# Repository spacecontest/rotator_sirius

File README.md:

# Направленная антенна с поворотным устройством для приема сигналов спутников
[Сайт проекта](http://openkoda.tilda.ws)

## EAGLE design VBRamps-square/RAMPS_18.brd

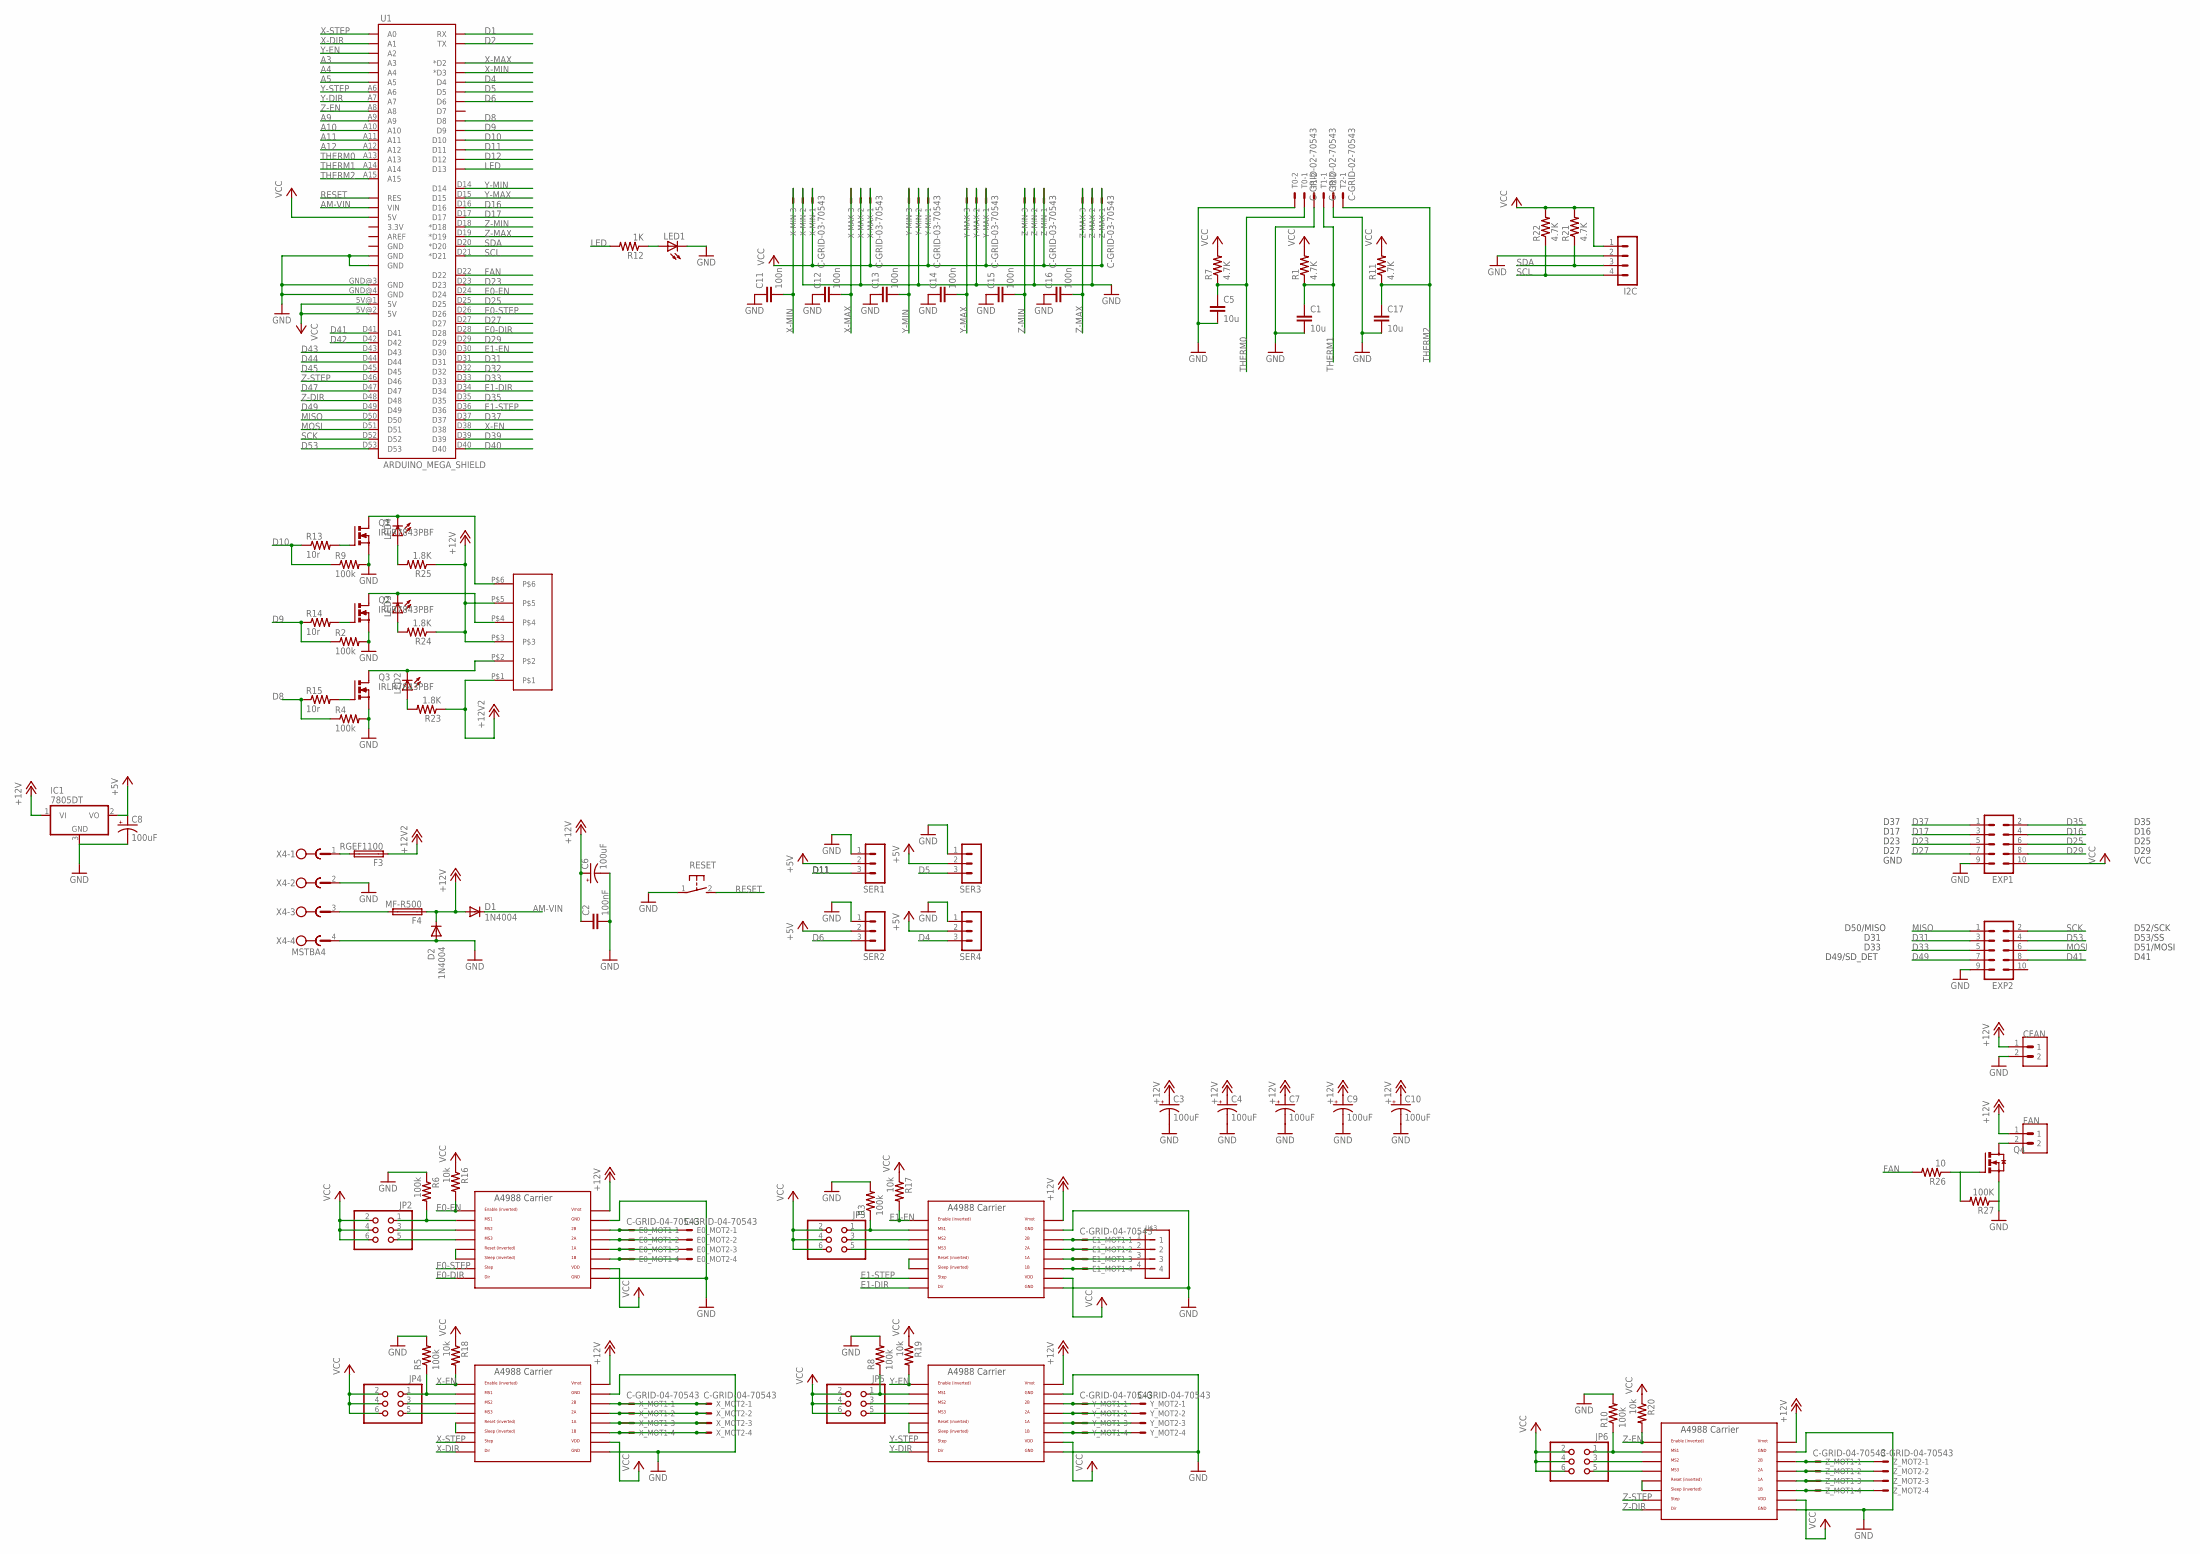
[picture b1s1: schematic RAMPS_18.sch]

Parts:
C1, C5, C17: 10u; C1206
C2: 100nF; C0805
C3, C4, C6, C7, C8, C9, C10: 100uF; 153CLV-0605
C11, C12, C13, C14, C15, C16: 100n; C0805
CFAN: CWF-2_D; CWF-2_P
D1, D2: 1N4004; DO41-10
E0_MOT1, E0_MOT2, E1_MOT1: C-GRID-04-70543; 70543-04
EXP1, EXP2: MA05-2; PAK100/2500-10
F3: RGEF1100
F4: MF-R500
FAN: CWF-2_D; CWF-2_P
HEAT_PORT: 282837-6
I2C: MA04-1
IC1: 7805DT; TO252
JP2, JP3, JP4, JP5, JP6: PINHD-2X3; 2X03
LED1, LED2, LED3, LED4: LEDCHIP-LED0805; CHIP-LED0805
Q1, Q2, Q3: IRLR7843PBF; D-PAK_TO252AA
Q4: N_MOSFET_SOT23; SOT23
R1, R7, R11, R21, R22: 4.7K; R1206
R2, R4, R9: 100k; R0805
R3, R5, R6, R8, R10: 100k; R1206
R12: 1K; R0805
R13, R15: 10r; R0805
R14: 10r; M0805
R16, R17, R18, R19, R20: 10k; R1206
R23, R24, R25: 1.8K; R0805
R26: 10; R1206
R27: 100K; R1206
RESET: 31-XX; B3F-31XX
SER1, SER2, SER3, SER4: 3PIN-HEADER
T0, T1, T2: C-GRID-02-70543; 70543-02
U1: ARDUINO_MEGA_SHIELD
U$3: CWF-4_D; CWF-4_P
U$4, U$5, U$6, U$7, U$8: A4988BREAKOUT
X4: MSTBA4
X-MAX: C-GRID-03-70543; 70543-03
X-MIN: C-GRID-03-70543; 70543-03
X_MOT1, X_MOT2: C-GRID-04-70543; 70543-04
Y-MAX: C-GRID-03-70543; 70543-03
Y-MIN: C-GRID-03-70543; 70543-03
Y_MOT1, Y_MOT2: C-GRID-04-70543; 70543-04
Z-MAX: C-GRID-03-70543; 70543-03
Z-MIN: C-GRID-03-70543; 70543-03
Z_MOT1, Z_MOT2: C-GRID-04-70543; 70543-04

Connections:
+5V: C8.+, IC1.2 (VO), SER1.2, SER2.2, SER3.2, SER4.2
+12V: C2.1, C3.+, C4.+, C6.+, C7.+, C9.+, C10.+, CFAN.1, D1.A, D2.C, F4.P$1 (1), FAN.1, HEAT_PORT.P$3, HEAT_PORT.P$5, IC1.1 (VI), R24.1, R25.1, U$4.VMOT, U$5.VMOT, U$6.VMOT, U$7.VMOT, U$8.VMOT
+12V2: F3.P$1 (1), HEAT_PORT.P$1, R23.1
A3: U1.A3
A4: U1.A4
A5: U1.A5
A9: U1.A9
A10: U1.A10
A11: U1.A11
A12: U1.A12
AM-VIN: D1.C, U1.VIN
D1: U1.RX
D2: U1.TX
D4: SER4.3, U1.D4
D5: SER3.3, U1.D5
D6: SER2.3, U1.D6
D8: R4.1, R15.1, U1.D8
D9: R2.1, R14.1, U1.D9
D10: R9.1, R13.1, U1.D10
D11: SER1.3, U1.D11
D12: U1.D12
D16: EXP1.4, U1.D16
D17: EXP1.3, U1.D17
D23: EXP1.5, U1.D23
D25: EXP1.6, U1.D25
D27: EXP1.7, U1.D27
D29: EXP1.8, U1.D29
D31: EXP2.3, U1.D31
D32: U1.D32
D33: EXP2.5, U1.D33
D35: EXP1.2, U1.D35
D37: EXP1.1, U1.D37
D39: U1.D39
D40: U1.D40
D41: EXP2.8, U1.D41
D42: U1.D42
D43: U1.D43
D44: U1.D44
D45: U1.D45
D47: U1.D47
D49: EXP2.7, U1.D49
D53: EXP2.4, U1.D53
E0-DIR: U1.D28, U$4.DIR
E0-EN: R16.2, U1.D24, U$4.EN
E0-STEP: U1.D26, U$4.STEP
E1-DIR: U1.D34, U$5.DIR
E1-EN: R17.2, U1.D30, U$5.EN
E1-STEP: U1.D36, U$5.STEP
FAN: R26.2, U1.D22
GND: C1.2, C2.2, C3.-, C4.-, C5.2, C6.-, C7.-, C8.-, C9.-, C10.-, C11.1, C12.1, C13.1, C14.1, C15.1, C16.1, C17.2, CFAN.2, D2.A, EXP1.9, EXP2.9, I2C.2, IC1.3 (GND), LED1.C, Q1.3 (S), Q2.3 (S), Q3.3 (S), Q4.2 (S), R2.2, R3.2, R4.2, R5.2, R6.1, R8.2, R9.2, R10.2, R27.1, RESET.1, SER1.1, SER2.1, SER3.1, SER4.1, T0.2, T1.2, T2.2, U1.GND@0 (GND), U1.GND@1 (GND), U1.GND@3 (GND), U1.GND@4 (GND), U$4.GND, U$4.GND@0 (GND), U$5.GND, U$5.GND@0 (GND), U$6.GND, U$6.GND@0 (GND), U$7.GND, U$7.GND@0 (GND), U$8.GND, U$8.GND@0 (GND), X4.2, X4.4, X-MAX.2, X-MIN.2, Y-MAX.2, Y-MIN.2, Z-MAX.2, Z-MIN.2
LED: R12.2, U1.D13
MISO: EXP2.1, U1.D50
MOSI: EXP2.6, U1.D51
unnamed: HEAT_PORT.P$4, LED3.C, Q2.4 (D)
unnamed: E0_MOT1.1, E0_MOT2.1, U$4.2B
unnamed: E0_MOT1.2, E0_MOT2.2, U$4.2A
unnamed: JP2.1, R6.2, U$4.MS1
unnamed: JP2.5, U$4.MS3
unnamed: HEAT_PORT.P$6, LED4.C, Q1.4 (D)
unnamed: U$4.RST, U$4.SLP (SLEEP)
unnamed: JP2.3, U$4.MS2
unnamed: E0_MOT1.3, E0_MOT2.3, U$4.1A
unnamed: E0_MOT1.4, E0_MOT2.4, U$4.1B
unnamed: E1_MOT1.1, U$3.1, U$5.2B
unnamed: E1_MOT1.2, U$3.2, U$5.2A
unnamed: JP4.1, R5.1, U$6.MS1
unnamed: JP4.3, U$6.MS2
unnamed: E1_MOT1.3, U$3.3, U$5.1A
unnamed: JP5.3, U$7.MS2
unnamed: E1_MOT1.4, U$3.4, U$5.1B
unnamed: JP4.5, U$6.MS3
unnamed: U$6.RST, U$6.SLP (SLEEP)
unnamed: U$6.2B, X_MOT1.1, X_MOT2.1
unnamed: U$6.2A, X_MOT1.2, X_MOT2.2
unnamed: U$7.RST, U$7.SLP (SLEEP)
unnamed: U$5.RST, U$5.SLP (SLEEP)
unnamed: JP3.1, R3.1, U$5.MS1
unnamed: U$6.1A, X_MOT1.3, X_MOT2.3
unnamed: U$6.1B, X_MOT1.4, X_MOT2.4
unnamed: U$7.2B, Y_MOT1.1, Y_MOT2.1
unnamed: U$7.2A, Y_MOT1.2, Y_MOT2.2
unnamed: U$7.1A, Y_MOT1.3, Y_MOT2.3
unnamed: JP5.5, U$7.MS3
unnamed: LED2.A, R23.2
unnamed: JP5.1, R8.1, U$7.MS1
unnamed: JP3.5, U$5.MS3
unnamed: JP3.3, U$5.MS2
unnamed: U$7.1B, Y_MOT1.4, Y_MOT2.4
unnamed: JP6.3, U$8.MS2
unnamed: U$8.RST, U$8.SLP (SLEEP)
unnamed: JP6.5, U$8.MS3
unnamed: JP6.1, R10.1, U$8.MS1
unnamed: U$8.2B, Z_MOT1.1, Z_MOT2.1
unnamed: U$8.2A, Z_MOT1.2, Z_MOT2.2
unnamed: U$8.1A, Z_MOT1.3, Z_MOT2.3
unnamed: U$8.1B, Z_MOT1.4, Z_MOT2.4
unnamed: LED3.A, R24.2
unnamed: LED1.A, R12.1
unnamed: Q2.1 (G), R14.2
unnamed: Q1.1 (G), R13.2
unnamed: Q3.1 (G), R15.2
unnamed: LED4.A, R25.2
unnamed: HEAT_PORT.P$2, LED2.C, Q3.4 (D)
unnamed: F3.P$2 (2), X4.1
unnamed: F4.P$2 (2), X4.3
unnamed: FAN.2, Q4.3 (D)
unnamed: Q4.1 (G), R26.1, R27.2
RESET: RESET.2 (S), U1.RES
SCK: EXP2.2, U1.D52
SCL: I2C.4, R22.1, U1.D21 (*D21)
SDA: I2C.3, R21.1, U1.D20 (*D20)
THERM0: C5.1, R7.1, T0.1, U1.A13
THERM1: C1.1, R1.1, T1.1, U1.A14
THERM2: C17.1, R11.1, T2.1, U1.A15
VCC: EXP1.10, I2C.1, JP2.2, JP2.4, JP2.6, JP3.2, JP3.4, JP3.6, JP4.2, JP4.4, JP4.6, JP5.2, JP5.4, JP5.6, JP6.2, JP6.4, JP6.6, R1.2, R7.2, R11.2, R16.1, R17.1, R18.1, R19.1, R20.1, R21.2, R22.2, U1.5V@0 (5V), U1.5V@1 (5V), U1.5V@2 (5V), U$4.VDD, U$5.VDD, U$6.VDD, U$7.VDD, U$8.VDD, X-MAX.1, X-MIN.1, Y-MAX.1, Y-MIN.1, Z-MAX.1, Z-MIN.1
X-DIR: U1.A1, U$6.DIR
X-EN: R18.2, U1.D38, U$6.EN
X-MAX: C12.2, U1.D2 (*D2), X-MAX.3
X-MIN: C11.2, U1.D3 (*D3), X-MIN.3
X-STEP: U1.A0, U$6.STEP
Y-DIR: U1.A7, U$7.DIR
Y-EN: R19.2, U1.A2, U$7.EN
Y-MAX: C14.2, U1.D15, Y-MAX.3
Y-MIN: C13.2, U1.D14, Y-MIN.3
Y-STEP: U1.A6, U$7.STEP
Z-DIR: U1.D48, U$8.DIR
Z-EN: R20.2, U1.A8, U$8.EN
Z-MAX: C16.2, U1.D19 (*D19), Z-MAX.3
Z-MIN: C15.2, U1.D18 (*D18), Z-MIN.3
Z-STEP: U1.D46, U$8.STEP

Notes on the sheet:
D37
D35
D17
D16
D23
D25
D27
D29
GND
VCC
D50/MISO
D52/SCK
D31
D53/SS
D33
D51/MOSI
D49/SD_DET
D41

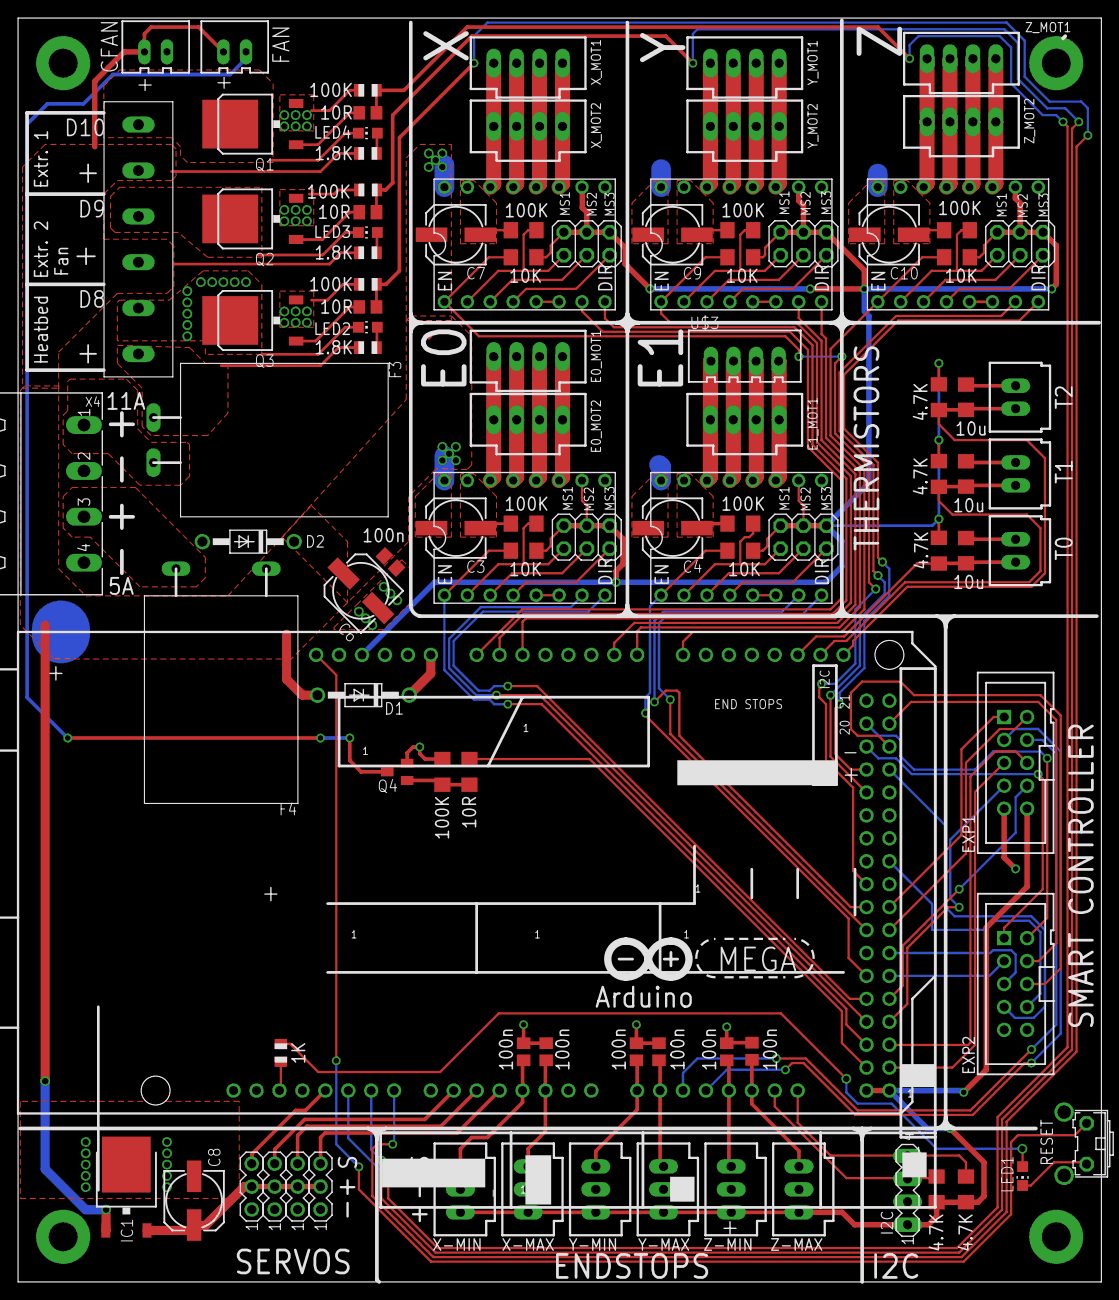
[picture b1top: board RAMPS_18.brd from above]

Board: 2 copper layers, 120.0 x 140.0 mm, 99 parts (1 on the bottom side), 112 nets.

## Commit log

2019-03-08 stl added
2019-03-09 Uploading GUI
2019-03-09 ino added
2019-03-11 ramps added

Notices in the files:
VBRamps-square/RAMPS_18.brd:
GPL v3
Copyright 2011 Johnny Russell - UltiMachine
